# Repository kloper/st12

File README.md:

* README for ST12

I am working on my own soldering station based on HAKKO T12 cartriges. 
Electronics is related to the one found on EEVBlog forum
https://www.eevblog.com/forum/reviews/t12-stm32-v2-1s-soldering-station-controller-schematic-etc/

Firmware will be built from scratch.
Work in progress.

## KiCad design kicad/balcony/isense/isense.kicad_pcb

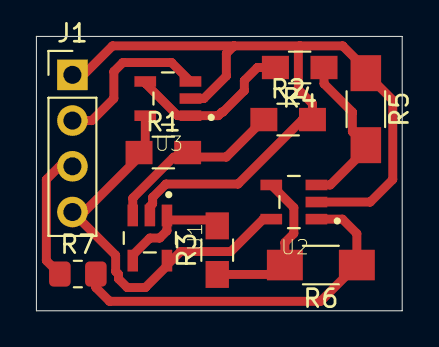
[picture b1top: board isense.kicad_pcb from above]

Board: 2 copper layers, 20.3 x 15.2 mm, 11 parts (0 on the bottom side), 10 nets.

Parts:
J1: IN; Pin_Header_Straight_1x04_Pitch2.54mm
R1, R2: 7.5K; R_0805_HandSoldering
R3, R4: 20K; R_0805_HandSoldering
R5, R6: 470K; R_1206_HandSoldering
R7: 100K; R_0805_2012Metric_Pad1.20x1.40mm_HandSolder
U1, U2, U3: OPA237NA_250; SOT95P280X145-5N

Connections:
+5V: J1.4, R1.1, U1.5, U2.5, U3.5
/VIN: J1.2, U3.3
/VOUT: J1.3, R7.1
GND: J1.1, R2.2, R5.1, U1.2, U2.2, U3.2
unnamed: R1.2, R2.1, U1.3
unnamed: R3.1, R6.2, U2.4
unnamed: R3.2, U1.1, U1.4
unnamed: R4.1, R5.2, U2.3
unnamed: R4.2, U3.1, U3.4
unnamed: R6.1, R7.2, U2.1

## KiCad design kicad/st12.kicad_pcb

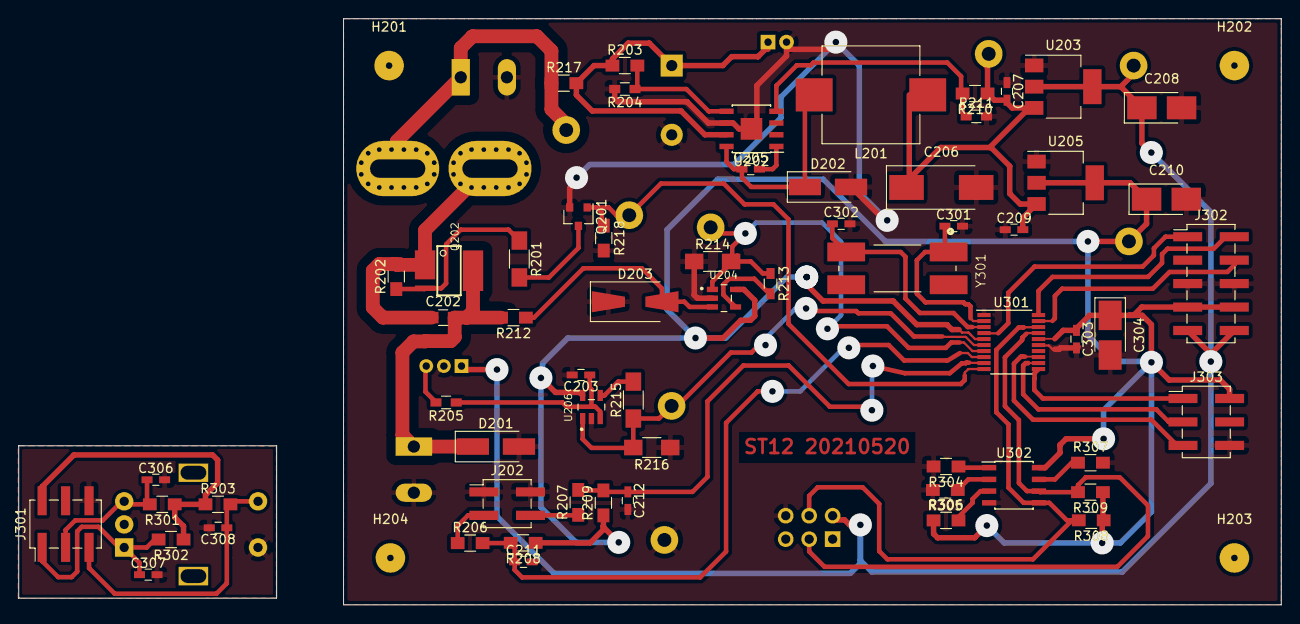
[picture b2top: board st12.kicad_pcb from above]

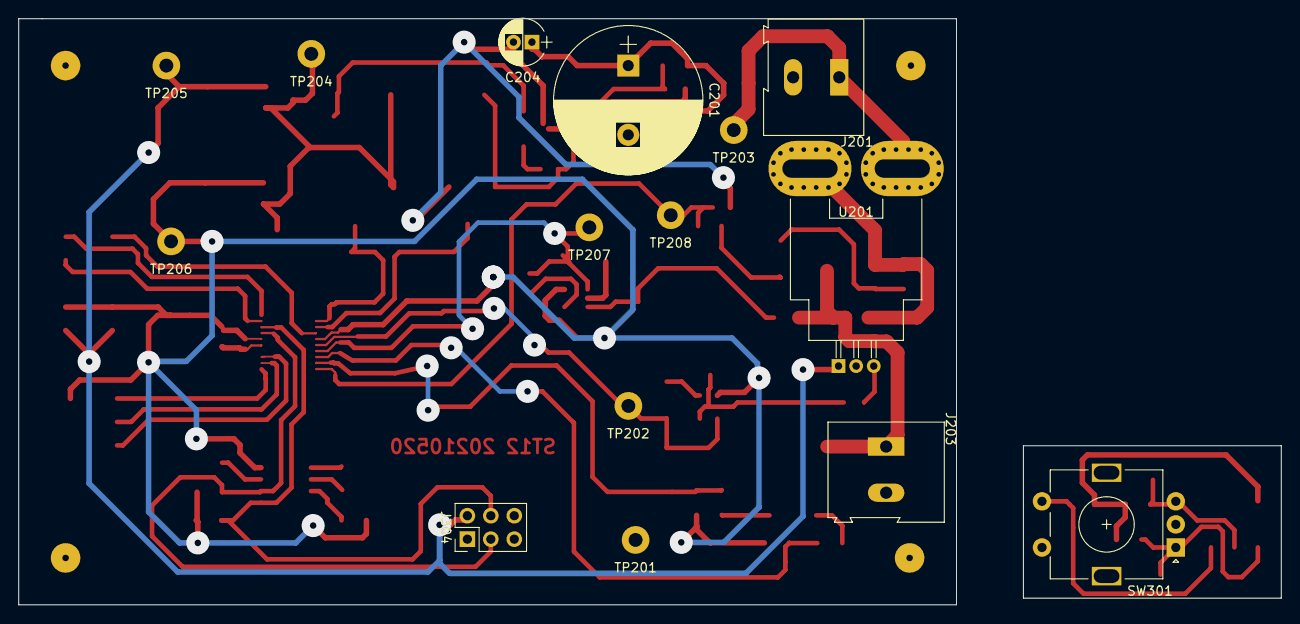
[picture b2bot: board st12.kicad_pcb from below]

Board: 2 copper layers, 136.8 x 63.5 mm, 81 parts (15 on the bottom side), 45 nets.

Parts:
C201: 220uF 35V; CP_Radial_D16.0mm_P7.50mm
C202: 1uF; C_0805_HandSoldering
C203, C207, C209, C303, C306, C307, C308: 100nF; C_0603_HandSoldering
C204: 10uF 35V; CP_Radial_D5.0mm_P2.00mm
C205, C211, C212: 10nF; C_0603_HandSoldering
C206: 220uF 6V; CP_Tantalum_Case-X_EIA-7343-43_Hand
C208, C210: 10uF; CP_Tantalum_Case-B_EIA-3528-21_Hand
C301, C302: 22pF; C_0603_HandSoldering
C304: 4.7uF; CP_Tantalum_Case-B_EIA-3528-21_Hand
D201, D202: 30V 0.5A; D_SMA_Handsoldering
D203: RS1M; D_SMA-SMB_Universal_Handsoldering
H201, H202, H203, H204: MountingHole; MountingHole_3.2mm_M3
J201: Conn_01x02_Male; TerminalBlock_Altech_AK300-2_P5.00mm
J202: T12_Sense; Pin_Header_Straight_2x02_Pitch2.54mm_SMD
J203: T12_POWER; TerminalBlock_Altech_AK300-2_P5.00mm
J301: ROT_OUT; Pin_Header_Straight_2x03_Pitch2.54mm_SMD
J302: DEBUG; Pin_Header_Straight_2x05_Pitch2.54mm_SMD
J303: ROT_IN; Pin_Header_Straight_2x03_Pitch2.54mm_SMD
J304: DISPLAY; Pin_Header_Straight_2x03_Pitch2.54mm
L201: 15uH; L_10.4x10.4_H4.8
Q201: 2N7002; SOT-23
Q202: FDS4435BZ; SO08-E3
R201, R214, R215, R216: 1K; R_1206_HandSoldering
R202: 2K; R_0805_HandSoldering
R203, R210: 100K; R_0805_HandSoldering
R204: 10K; R_0603_HandSoldering
R205: 47; R_0603_HandSoldering
R206, R207, R208, R209, R212, R218, R301, R302, R303, R304, R305, R306, R307, R308, R309: 7.5K; R_0805_HandSoldering
R211: 24K; R_0603_HandSoldering
R213: 249K; R_0603_HandSoldering
R217: 0; R_0805_HandSoldering
SW301: Encoder; RotaryEncoder_Alps_EC11E-Switch_Vertical_H20mm
TP201: GND; Measurement_Point_Round-TH_Big
TP202: ISENSE; Measurement_Point_Round-TH_Big
TP203: 24V; Measurement_Point_Round-TH_Big
TP204: 6V; Measurement_Point_Round-TH_Big
TP205: 5V; Measurement_Point_Round-TH_Big
TP206: 3.3V; Measurement_Point_Round-TH_Big
TP207: TSENSE; Measurement_Point_Round-TH_Big
TP208: CTRL; Measurement_Point_Round-TH_Big
U201: ACS756xCB-050B-PFF; Allegro_CB_PFF
U202: TPS5430DDAR; SOIC-8-1EP_3.9x4.9mm_Pitch1.27mm
U203: AMS1117-5.0; SOT-223-3_TabPin2
U204, U206: OPA237NA_250; SOT95P280X145-5N
U205: AMS1117-3.3; SOT-223-3_TabPin2
U301: STM32F030F4Px; TSSOP-20_4.4x6.5mm_Pitch0.65mm
U302: 24LC1025; SOIC-8_3.9x4.9mm_Pitch1.27mm
Y301: MA-506-8MHz; XTAL_MA-506_4.0000M-C3_ROHS

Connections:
+3V3: C210.1, C303.1, C304.1, J302.7, J302.8, J303.2, R208.1, R209.1, R306.1, R308.1, R309.1, TP206.1, U204.5, U205.2, U206.5, U301.5, U301.16, U302.8
+5V: C208.1, J302.9, J302.10, J304.2, TP205.1, U201.1, U203.2
+6V: C206.1, C207.2, C209.2, L201.1, R210.1, TP204.1, U203.3, U205.3
+24V: J201.1, R217.1, TP203.1, U201.4
/control/ROTA: C307.1, J301.1, R302.2, SW301.A
/control/ROTA_IN: J303.1, U301.11
/control/ROTB: C306.1, J301.3, R301.2, SW301.B
/control/ROTB_IN: J303.3, U301.12
/control/ROTP: C308.1, J301.5, R303.2, SW301.S1
/control/ROTP_IN: J303.5, U301.13
/control/ROT_GND: C306.2, C307.2, C308.2, J301.6, SW301.C, SW301.S2
/control/ROT_VCC: J301.2, R301.1, R302.1, R303.1
/control/SCL: J304.3, R309.2, U301.17, U302.6
/control/SDA: J304.4, R308.2, U301.18, U302.5
/control/SWCLK: J302.2, U301.20
/control/SWDIO: J302.4, U301.19
/control/~RST~: J302.1, U301.4
/power/COLD: J202.4, R207.1
/power/SHAKE: J202.3, R206.1
/power/V24AVAIL: R203.2, R204.1, U202.5
/power/V24HEATER: C202.2, D201.1, J203.1, Q202.58, R212.2
/power/V24SRC: C201.1, C204.1, R203.1, R217.2, U202.7
/power/VSENS: R210.2, R211.1, U202.4
COLD_SENSE: C212.1, R207.2, R209.2, U301.9
GND: C201.2, C203.2, C204.2, C206.2, C207.1, C208.2, C209.1, C210.2, C211.2, C212.2, C301.2, C302.2, C303.2, C304.2, D201.2, D202.2, D203.1, J201.2, J202.1, J202.2, J203.2, J302.5, J302.6, J303.6, J304.6, Q201.2, R204.2, R211.2, R214.1, R216.1, R218.2, R304.2, R305.2, R307.2, TP201.1, U201.2, U202.6, U202.9, U203.1, U204.2, U205.1, U206.2, U301.1, U301.15, U302.4
HEATER_CTL: Q201.1, R218.1, TP208.1, U301.10
I_SENSE: R215.1, R216.2, TP202.1, U206.1, U301.6
unnamed: C202.1, Q202.13, R202.2, U201.5
unnamed: C203.1, R205.1, U206.3
unnamed: C205.1, D202.1, L201.2, U202.8
unnamed: C205.2, U202.1
unnamed: C301.1, U301.2, Y301.1
unnamed: C302.1, U301.3, Y301.2
unnamed: D203.2, R212.1, U204.3
unnamed: Q201.3, R201.2
unnamed: Q202.4, R201.1, R202.1
unnamed: R205.2, U201.3
unnamed: R213.2, U204.4
unnamed: R215.2, U206.4
unnamed: R304.1, U302.1
unnamed: R305.1, U302.2
unnamed: R306.2, U302.3
unnamed: R307.1, U302.7
SHAKE_SENSE: C211.1, R206.2, R208.2, U301.8
T_SENSE: R213.1, R214.2, TP207.1, U204.1, U301.7

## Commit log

2021-06-07 Initial import of ST12 kicad files.
2021-06-10 Add current sensor balcony patch
2021-06-10 Add BMP->ST-Link2 debug adapter
2021-06-10 Fix ST12 schematics with current sensor (tested on balcony patch)
2021-06-10 Move all kicad stuff under kicad folder
2021-06-10 Add biased non-inverting opamp calculator
2021-06-10 Add LICENSE file
2021-06-11 Initial import of ST12 firmware
2021-06-18 Rename gdbinit.gdb -> gdb_load.gdb
2021-06-18 Make gdb_load.gdb to break at main() + add gdb_attach.gdb for debug
2021-06-18 Implement input ADC management with DMA and periodic timer
2021-06-18 Introduce notes for keeping plans and bugs
2021-07-07 ADC code fixes + temperature calculations
2021-07-12 Start to implement proper exception management ...
    At this stage introduce own blocking handler for unmanaged
    exceptions. This one differs from handler provided by cm3
    by keeping exception number in local variable.
    Remove invocation of HSE, stay on HSI and 48MHz PLL. Switching
    to external clock quite frequently causes hard fault exceptions
    for unknown reason.
2021-07-12 Introduce I2C initialization and persistent configuration ...
    The persistent configuration is based on I2C attached EEPROM.
    The config is implemented as a structure in memory with write
    through functionality.
2021-07-18 Fixes in schematics (only) done during initial debug
2021-07-18 Introduce pato display support and rotary encoder support
2021-09-28 Decrease speed of I2C bus to 50KHz
    For yet unknown reason, STM32 interface gets NACKS from Pato display
    on startup, this leads libopencm3 I2C implentation to stall on I2C
    communication.
    Decreasing speed of the bus decreases chances of NACKS.
2021-09-28 Factor out I2C send and receive operations to be generic I2C code.
2021-09-28 Fix EEPROM memory address endian.
    Write and read operations to I2C EEPROM start from I2C write with two byte
    memory address of the desired operation. The address must be big endian.
2021-09-28 Introduce initial code for current monitoring.
2021-09-28 Introduce scale and offset for temperature conversion
2021-10-01 Introduce current scale and offset config parameters ...
    For fine tuning of the current measurement
2021-10-02 Remove read part of the query when printing on display ...
    Since latest pato USI does not require read transaction after write
    we can remove reading of unneeded info.
2021-10-02 Introduce support for ST12 handle shake sensor ...
    The shake sensor is simple mercury bulb that shorts middle point
    of 7.5K/7.5K voltage divider to ground. It is also connected to
    PA2. We use it in fashion similar to rotary encoder - declare
    PA2 as external interrupt source and just counting events on
    the line.
2021-10-23 Introduce config version ...
    Config version is included in total CRC calculation.
    Thus, bumping version causes the EEPROM reset to factory settings.
2021-10-23 Improve idle sensor detection and temperature drop
    This change causes temperature drop upon reaching idle state after
    predefined timeout. The idle state is canceled once shake sensor
    state change is detected.
2021-10-28 Rename main.c -> st12_main.c
2021-10-28 Remove "extern" from function prototypes in header files
2021-10-30 Change printing format and remove redundant printing conditions
2021-10-30 Add spin-off of term code from uv-timer
2021-10-31 Introduce temperature/current info widget
    Substitute regular print with similar functionality based on term library.
    The term_st12_temp_label_t now holds idle, temperature and current variables
    and is responsible for handling top line on the display.
    Rotary encoder events are now handled by widgets.
2021-10-31 Notes update
2021-10-31 Notebook update
2021-11-17 Bump version and add version check to reset config on bump
2021-11-17 Fix missing ending zero when sending data to display
    Pato protocol requires print data to end with zero character.
    ST12 display code could miss sending the last zero on even
    number of chars in the print string
2021-11-17 Introduce ST12 menu and make terminal changes specific to ST12
2021-11-17 Integrate ST12 menu with main
2021-11-26 Substitute -Os with -O1 which seems to work fine ...
    and not mess with timings in st12_i2c.c
2021-12-11 Add over-current indication support
2021-12-11 Various schematic fixes
2021-12-11 Add freecad case project
